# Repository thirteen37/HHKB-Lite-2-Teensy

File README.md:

# Teensy 2.0 replacement controller board for HHKB Lite 2

This is a QMK-compatible replacement controller for the [HHKB Lite
2](https://deskthority.net/wiki/HHKB_Lite), identified by model
numbers PD-KB200W/U or PD-KB200B/U.

This Lite version of the HHKB is a membrane keyboard and not exactly
popular compared to more expensive Professional versions that use
Topre switches. But the wiring is simple and is a good first project
for modding commercial keyboards.

This replacement uses a [Teensy
2.0](https://www.pjrc.com/store/teensy.html), which is cheap, has
plenty of pins, and works well with the [QMK
firmware](https://qmk.fm/). The entire controller board is replaced,
so you will lose the built-in USB hub. You will gain all the benefits
of the powerful QMK and similar Teensy-supported firmware.

## Steps

1. Acquire/fabricate the PCB.
2. Get the parts
3. Disassemble the keyboard.
4. Modify the USB cable you will be using and insert it into the Teensy.
5. Solder the components on to the board. Take care to leave enough
   room for the USB cable when soldering the Teensy.
6. Reconnect the flex cables and insulate the backplate.
7. Flash your firmware and test your keyboard.
8. Reassemble the shell.

### PCB fabrication

The fabrication-ready files are in `plots/`. Just send them to your
preferred fab. It is a pretty standard 1.6mm PCB with conservative via
and track parameters that just about any shop can handle.

You can also [order the PCBs through
PCBway](https://www.pcbway.com/project/shareproject/HHKB_Lite_2___Teensy_2_0_controller.html). With
their new user discount, you would only have to pay shipping.

### Parts

* 1 [Teensy 2.0](https://www.pjrc.com/store/teensy.html)
* 1 Molex Easy-On 14-pin 1.25mm pitch FFC connector 39-53-2145
* 1 Molex Easy-On 8-pin 1.25mm pitch FFC connector 39-53-2085
* 1/10" pitch thru-hole headers for Teensy
* (White?) Mini-USB cable for Teensy

The USB cable you get should have plastic plugs, because you will have
to shave them down later.

### Disassembly

The keyboard is held together by a few screws. Don't forget the screw
hiding under the label. When the shell is open, there are also further
one screw holding down the metal backplate and one screw each for
the PCBa.

The USB cable can be removed from the shell but does not need to be
detached from the PCB. We will be using another USB cable instead.

The flex cables can be eased out gently. There is no latching
mechanism.

### Modify the USB cable

The Mini-USB plug that goes to the Teensy needs to be shaved down to
save about 1mm of thickness.

### Soldering the board

My recommended order is:
1. Headers for Teensy on to the board
2. Molex connectors
3. Teensy

The Molex connectors are oriented in opposite directions, with pin 1
(the edge with a little notch) of each connector facing each
other. This is important because the flex cables and connectors are
single sided.

Note that the Teensy should be mounted upside down, on the same side
as the connectors. This is to save a couple of millimeters of space
from the stacked height of the connectors. You may have to trim down
the header pins after you've soldered on the Teensy. The USB cable
should still be able to fit.

### Connect flex cables and insulate the backplate

Connect the flex cables to the PCB. Note the orientation.

The metal backplate should be insulated, at least around the area of
the PCB, to minimize the risk of it shorting the board. I use a few
strips of electrical insulation tape here.

### Flash the firmware and test

Plug in the USB cable to your computer and flash the firmware. There's
a copy of the firmware with the default layout at
`firmware/hhkblite2.hex`.

Programming is done using [Teensy
Loader](https://www.pjrc.com/teensy/loader.html). Since the Teensy is
mounted upside down and the reset button no longer exposed, you can
short the `RST` and `GND` pins instead.

After a successful initial flash, you can use the `reset` key to enter
flashing mode instead of having to open the keyboard. On my default
configuration, the `reset` key is `Fn` + `Esc`.

After flashing, you should be able to type something. It's easiest to
just put the silicone membrane over the traces and try typing
something.

### Reassembly

The PCB here only uses one of the original PCB mounting screws. Route
the USB cable around the internal strain relief. Don't forget the
screw for the backplate.

You're done!

## PCB details

This is a [KiCad](https://kicad.org/) project, but you can find
the generated fabrication files in `plots/`. Just send them to your
preferred PCB factory.

The schematics are fairly straightforward, with 8 row pins and 14
column pins:

The PCB layout is likewise simple:

## Firmware

The configuration in `firmware/` can be uploaded to [Keyboard Firmware
Builder](https://kbfirmware.com/) to generate firmware for the
standard US QWERTY layout.

There will be a warning "Not every key has a unique position in the
wiring matrix". This can be ignored and it is due to both `Fn` keys
being wired exactly the same. You should take note of this when
designing your own layouts: it is not possible to assign different
keycodes to each `Fn` key as they are electrically indistinguishable.

The wiring matrix is a bit of a mess, as is typical of membrane
keyboards that do not have diodes to prevent ghosting: the matrix is
designed to minimize ghosting from common key combinations but will
never completely eliminate it.

The pin assignments are:

| Matrix    | Pin |
|-----------|-----|
| *Rows*    |     |
| 0         | F5  |
| 1         | F4  |
| 2         | F1  |
| 3         | F0  |
| 4         | B0  |
| 5         | B1  |
| 6         | B2  |
| 7         | B3  |
| *Columns* |     |
| 0         | F6  |
| 1         | F7  |
| 2         | B6  |
| 3         | B5  |
| 4         | B4  |
| 5         | D7  |
| 6         | D6  |
| 7         | D4  |
| 8         | D5  |
| 9         | C7  |
| 10        | C6  |
| 11        | D3  |
| 12        | D2  |
| 13        | D1  |

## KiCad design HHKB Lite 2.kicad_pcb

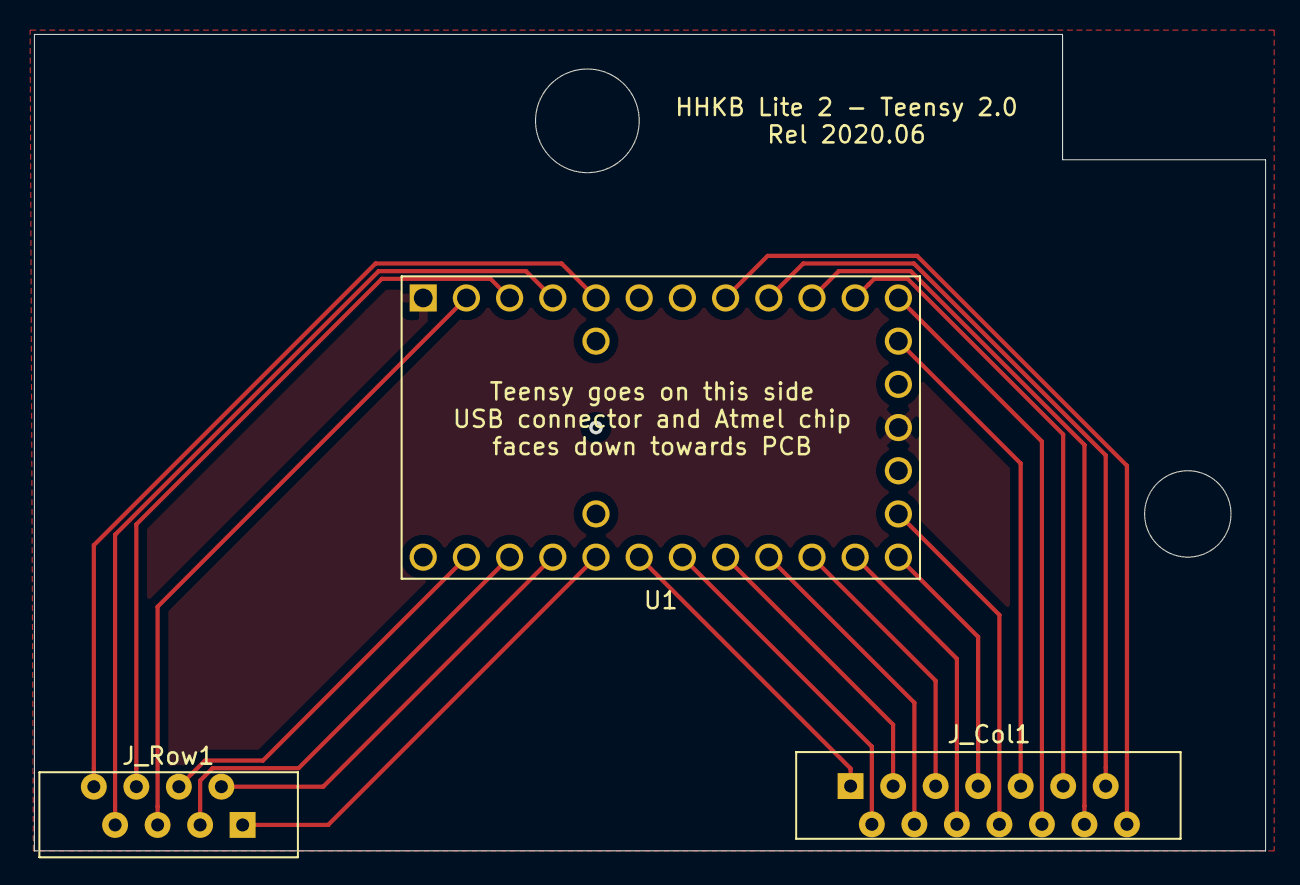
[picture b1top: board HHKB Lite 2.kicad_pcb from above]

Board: 2 copper layers, 72.4 x 48.0 mm, 3 parts (1 on the bottom side), 23 nets.

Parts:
J_Col1: Columns; Molex_Easy-On_39-53-2144_14-Contacts
J_Row1: Rows; Molex_Easy-On_39-53-2084_8-Contacts
U1: Teensy2.0_(C); Teensy2.0

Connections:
GND: U1.1, U1.15
unnamed: J_Col1.1, U1.24
unnamed: J_Col1.2, U1.23
unnamed: J_Col1.3, U1.22
unnamed: J_Col1.4, U1.21
unnamed: J_Col1.5, U1.20
unnamed: J_Col1.6, U1.19
unnamed: J_Col1.7, U1.18
unnamed: J_Col1.8, U1.17
unnamed: J_Col1.9, U1.13
unnamed: J_Col1.10, U1.12
unnamed: J_Col1.11, U1.11
unnamed: J_Col1.12, U1.10
unnamed: J_Col1.13, U1.9
unnamed: J_Col1.14, U1.8
unnamed: J_Row1.1, U1.25
unnamed: J_Row1.2, U1.26
unnamed: J_Row1.3, U1.27
unnamed: J_Row1.4, U1.28
unnamed: J_Row1.5, U1.2
unnamed: J_Row1.6, U1.3
unnamed: J_Row1.7, U1.4
unnamed: J_Row1.8, U1.5

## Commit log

2020-05-17 Squashed 'libs/teensy_library/' content from commit edea928
    git-subtree-dir: libs/teensy_library
    git-subtree-split: edea9289a33b800b6fc53c6b5248757f37890773
2020-05-17 Add Teensy library
2020-05-17 Squashed 'libs/teensy.pretty/' content from commit 67e6da4
    git-subtree-dir: libs/teensy.pretty
    git-subtree-split: 67e6da43dfdc7eb5902d2ab31cfd750425c47129
2020-05-17 Add Teensy footprint
2020-05-17 Add Molex Easy-On connector footprints
2020-05-17 Add README
2020-05-17 Firmware configuration
    Also with diagrams and instructions
2020-05-17 Generated PCB files
2020-05-17 Bug fix firmware
    Function key toggled to wrong layer
2020-05-19 Gitignore cache and backup
2020-05-19 Flip Teensy
2020-05-23 More detailed assembly instructions
2020-05-23 Illustrations for instructions
2020-05-23 Include basic firmware
2020-05-23 Pin assignments
2020-05-23 Move hex file into firmware directory
2020-05-23 Tweak PCB layout
    Adjust mounting holes. Update images.
2020-05-23 Add PCBway affiliate link
2020-05-24 Fix kbfirmware config
2021-11-10 Update README.md
    https://forum.kicad.info/t/warning-avoid-all-links-to-kicad-pcb-org-use-kicad-org/31521
